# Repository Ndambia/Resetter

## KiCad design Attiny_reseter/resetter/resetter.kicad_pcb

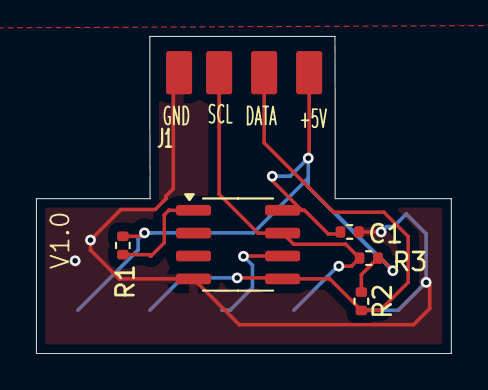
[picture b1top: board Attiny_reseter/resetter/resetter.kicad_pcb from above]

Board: 2 copper layers, 23.1 x 17.6 mm, 7 parts (1 on the bottom side), 6 nets.

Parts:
C1: 0.1; R_0402_1005Metric
J1: Conn_01x04_Pin; TerminalBlock_MaiXu_MX126-5.0-04P_1x04_P5.00mm
J2: Conn_01x05_Pin; TerminalBlock_MaiXu_MX126-5.0-05P_1x05_P5.00mm
R1: 10K; R_0402_1005Metric
R2, R3: 4.7K; R_0402_1005Metric
U1: ATtiny25-20SS; SOIC-8_3.9x4.9mm_P1.27mm

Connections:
+5V: C1.1, J1.4, J2.5, R1.1, R2.1, R3.1, U1.8 (VCC)
GND: C1.2, J1.1, J2.1, U1.4 (GND)
MISO: J2.3, U1.6 (PB1)
MOSI: J1.3, J2.4, R2.2, U1.5 (AREF/PB0)
unnamed: R1.2, U1.1 (~RESET/PB5)
SCL: J1.2, J2.2, R3.2, U1.7 (PB2)

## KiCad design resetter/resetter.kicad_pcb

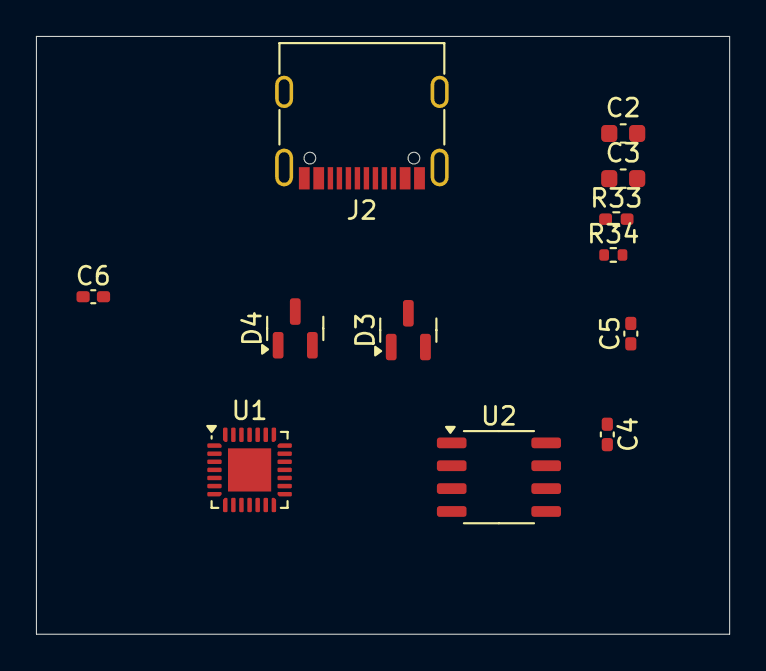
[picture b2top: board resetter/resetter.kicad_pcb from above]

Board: 2 copper layers, 38.5 x 33.2 mm, 12 parts (0 on the bottom side), 6 nets, no tracks yet.

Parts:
C2: 0.47u; C_0603_1608Metric
C3: 0.1u; C_0603_1608Metric
C4: 10n; C_0402_1005Metric_Pad0.74x0.62mm_HandSolder
C5, C6: 22p; C_0402_1005Metric_Pad0.74x0.62mm_HandSolder
D3, D4: SP0502BAHT; SOT-23
J2: USB_C_Receptacle_USB2.0; USB_C_Receptacle_G-Switch_GT-USB-7010ASV
R33: 4.7k; R_0402_1005Metric_Pad0.72x0.64mm_HandSolder
R34: 4.7k; R_0402_1005Metric
U1: ATmega328-MM; QFN-28-1EP_4x4mm_P0.45mm_EP2.4x2.4mm
U2: CH340N; SOP-8_3.9x4.9mm_P1.27mm

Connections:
+5V: C2.1, C3.1, J2.A4 (VBUS), J2.A9 (VBUS), J2.B4 (VBUS), J2.B9 (VBUS), U1.3 (VCC), U1.16 (AVCC), U2.5 (VCC)
/D+: D3.1 (K), J2.A6 (D+), J2.B6 (D+)
/D-: D3.2 (K), J2.A7 (D-), J2.B7 (D-)
GND: C2.2, C3.2, C4.1, C5.1, C6.1, D3.3 (A), D4.3 (A), J2.A1 (GND), J2.A12 (GND), J2.B1 (GND), J2.B12 (GND), J2.S1 (SHIELD), R33.1, R34.1, U1.4 (GND), U1.18 (GND), U1.29 (GND), U2.3 (GND)
unnamed: D4.1 (K), D4.2 (K), J2.A5 (CC1), J2.B5 (CC2), R33.2, R34.2
unnamed: C4.2, U2.8 (V3)

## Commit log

2026-03-07 New deseign
2026-03-13 Add initial README with project title
